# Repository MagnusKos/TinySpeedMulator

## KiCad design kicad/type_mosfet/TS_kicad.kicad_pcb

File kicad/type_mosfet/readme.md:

Legacy
 It's working. Kinda...
 Has some problems with a phantom powering, that comes from an pulse-wire, when where are externally-generated pulses on it.

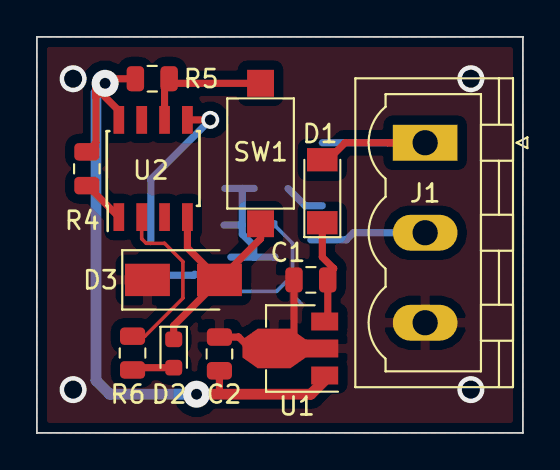
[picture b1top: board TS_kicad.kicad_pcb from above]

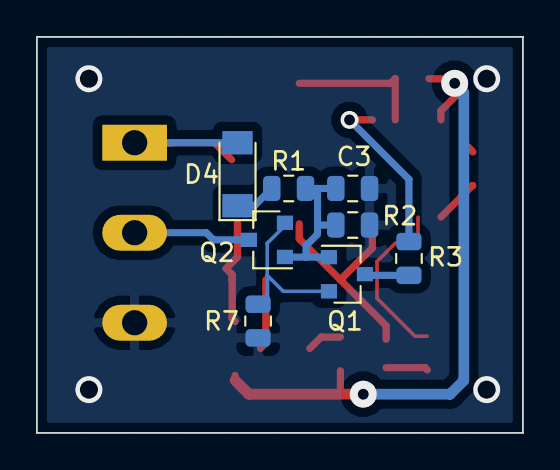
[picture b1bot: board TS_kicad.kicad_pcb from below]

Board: 2 copper layers, 27.0 x 22.0 mm, 20 parts (8 on the bottom side), 15 nets.

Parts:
C1: 1u; C_0805_2012Metric
C2, C3: 0.15; C_0805_2012Metric
D1, D4: LL4148; D_MiniMELF
D2: LED_Small; LED_0603_1608Metric
D3: SS16; D_SMA
J1: Conn_01x03; PhoenixContact_MSTBVA_2,5_3-G_1x03_P5.00mm_Vertical
Q1, Q2: 2N7002; SOT-23
R1, R6: 1k; R_0805_2012Metric
R2: 100k; R_0805_2012Metric
R3: 100; R_0805_2012Metric
R4, R5: 10k; R_0805_2012Metric
R7: 470k; R_0805_2012Metric
SW1: SW_Push; SW_SPST_CK_RS282G05A3
U1: L78L05_SOT89; SOT-89-3
U2: ATtiny13A-SSU; SOIC-8_3.9x4.9mm_P1.27mm

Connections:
+5V: C2.1, R4.1, R5.2, U1.1, U2.8
+12V: C1.1, D1.1, U1.3
/SIG: Q1.3, R3.1
/SIG_OUT: J1.2, Q2.3
GND: C1.2, C2.2, C3.2, D3.1, J1.3, R2.2, R7.1, U1.2
GNDD: D2.1, D3.2, SW1.2, U2.4
unnamed: C3.1, Q1.1, Q2.1, R1.1, R2.1
unnamed: D2.2, R6.1
unnamed: D4.1, R1.2
unnamed: Q1.2, Q2.2, R7.2
unnamed: R3.2, U2.5
unnamed: R4.2, U2.1
unnamed: R5.1, SW1.1, U2.6
unnamed: R6.2, U2.2
VCC: D1.2, D4.2, J1.1

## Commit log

2019-02-06 First working commit Generator goes without prescaler from 255 to 0 in OCR0A
2019-02-18 added lower freq, generator jumps through 3 timer prescalers for more accurate speed up/slow down
2023-01-20 THE First Commit Just a bunch of files, very ugly, not so useful
2023-01-20 Makin' movin' Rearranged files for a better view. It's a good start for the continuing of this old project.
2023-01-20 New schematics Reworked an old circuit. The new one uses relay, but there could be some current-related issues. Needs to be prototyped and tested.
